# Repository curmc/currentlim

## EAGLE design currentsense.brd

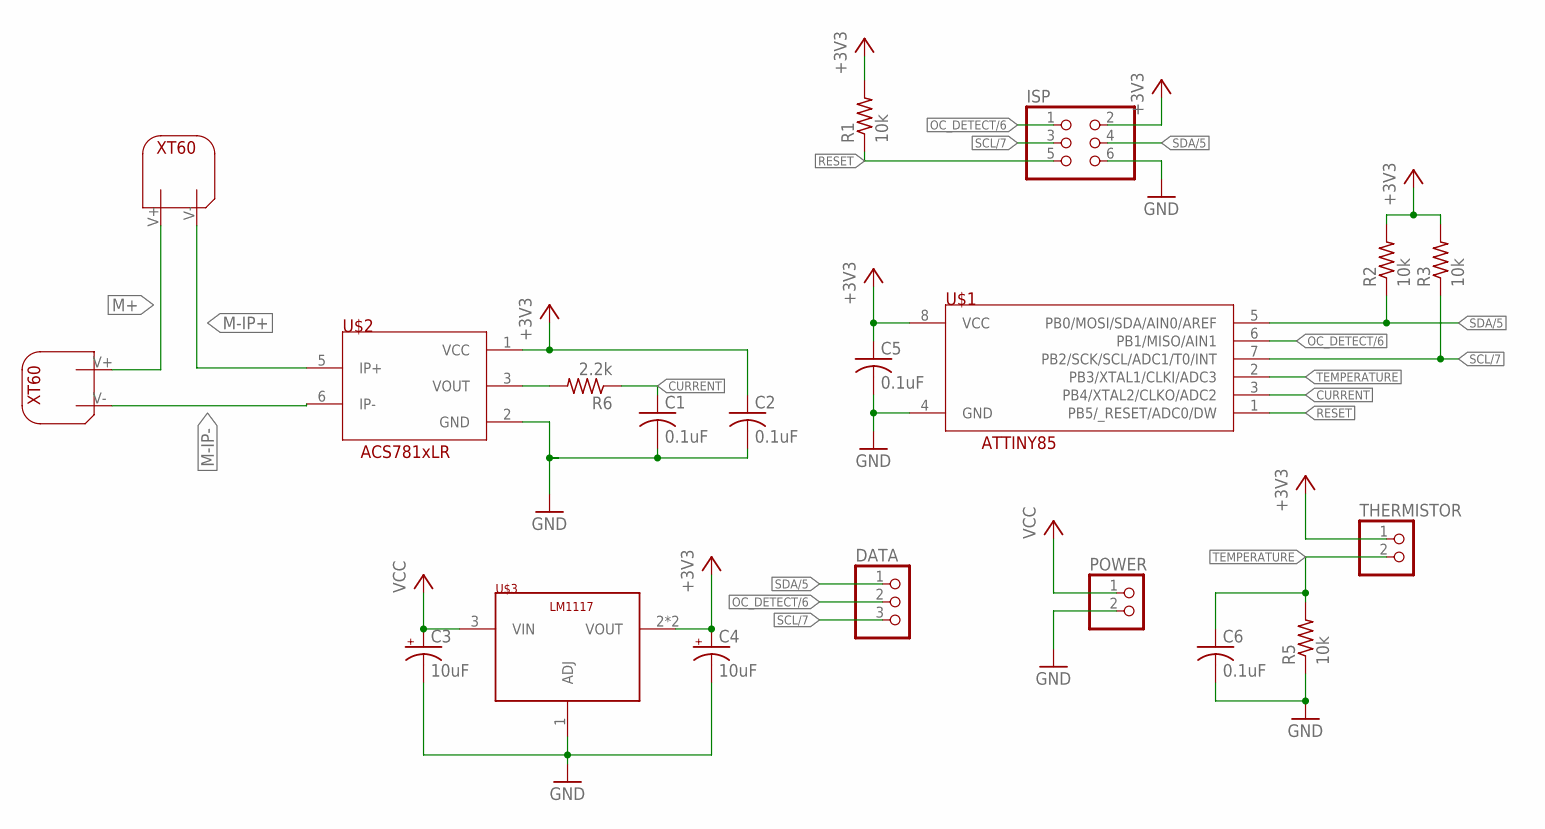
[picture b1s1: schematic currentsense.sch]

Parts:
C1, C2, C5, C6: 0.1uF; C0805
C3, C4: 10uF; E2,5-6
DATA: PINHD-1X3; 1X03
ISP: PINHD-2X3; 2X03
POWER: PINHD-1X2; 1X02
R1, R2, R3, R5: 10k; M0805
R6: 2.2k; M0805
THERMISTOR: PINHD-1X2; 1X02
U$1: ATTINY85V-10SUR; SOIC8
U$2: ACS781LLRTR-050B-T_M; 7-PSOF-EXTENDED
U$3: LM1117; SOT223
U$4, U$5: XT60-RA; XT60_RA

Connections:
+3V3: C2.1, C4.+, C5.1, ISP.2, R1.2, R2.2, R3.2, THERMISTOR.1, U$1.8 (VCC), U$2.1 (VCC), U$3.2 (VOUT), U$3.4 (VOUT)
CURRENT: C1.1, R6.1, U$1.3 (PB4/XTAL2/CLKO/ADC2)
GND: C1.2, C2.2, C3.-, C4.-, C5.2, C6.2, ISP.6, POWER.2, R5.1, U$1.4 (GND), U$2.2 (GND), U$3.1 (ADJ)
M+: U$4.V+, U$5.V+
M-IP+: U$2.5 (IP+), U$4.V-
M-IP-: U$2.6 (IP-), U$5.V-
unnamed: R6.2, U$2.3 (VOUT)
OC_DETECT/6: DATA.2, ISP.1, U$1.6 (PB1/MISO/AIN1)
RESET: ISP.5, R1.1, U$1.1 (PB5/_RESET/ADC0/DW)
SCL/7: DATA.3, ISP.3, R3.1, U$1.7 (PB2/SCK/SCL/ADC1/T0/INT)
SDA/5: DATA.1, ISP.4, R2.1, U$1.5 (PB0/MOSI/SDA/AIN0/AREF)
TEMPERATURE: C6.1, R5.2, THERMISTOR.2, U$1.2 (PB3/XTAL1/CLKI/ADC3)
VCC: C3.+, POWER.1, U$3.3 (VIN)

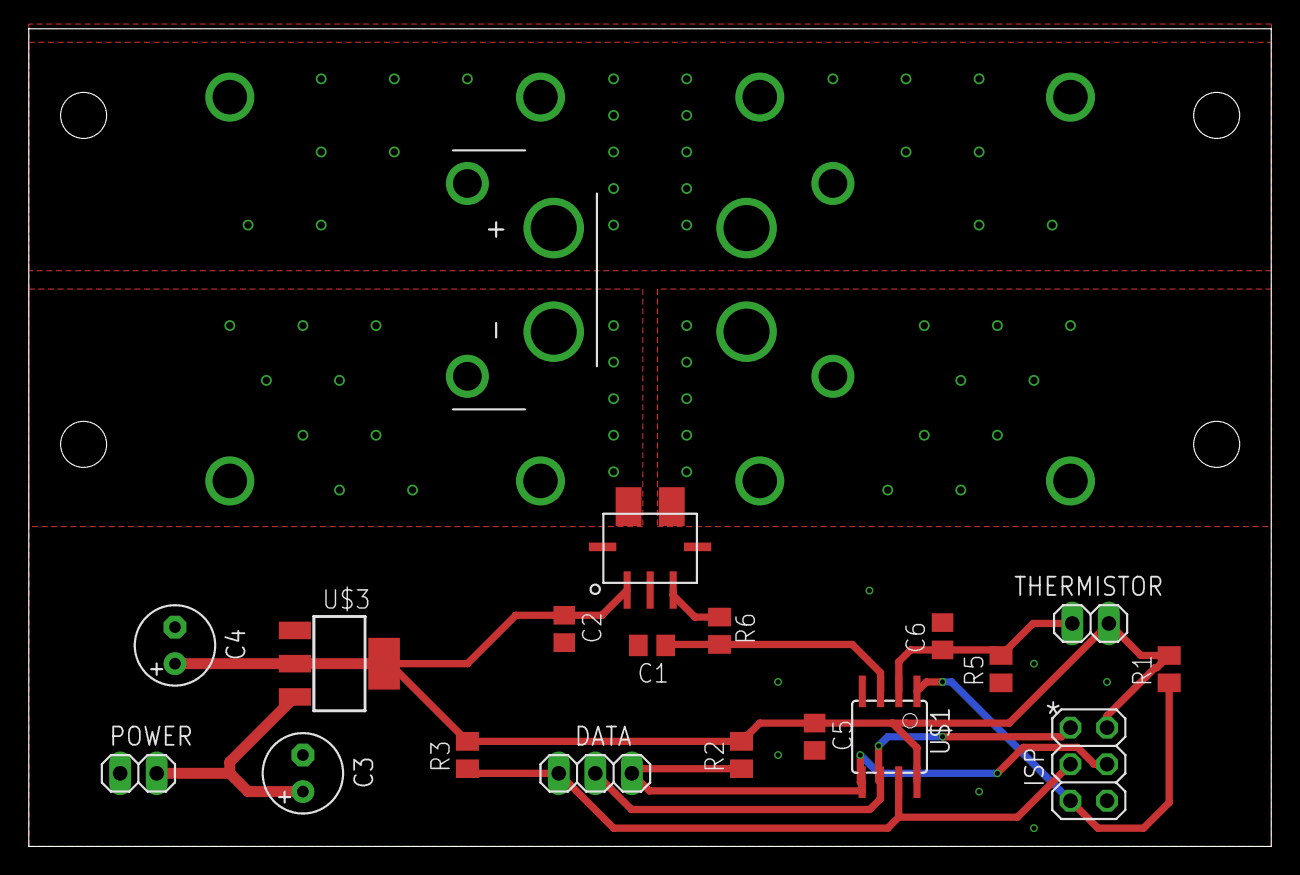
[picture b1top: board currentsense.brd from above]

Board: 4 copper layers, 86.3 x 56.8 mm, 20 parts (1 on the bottom side), 13 nets.

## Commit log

2020-01-28 relay n stuff
2020-02-29 current sense - finish sch, prelim brd layout
2020-03-03 more layout work
2020-03-03 add board files
2020-03-03 minor error
2020-03-03 gerberos
